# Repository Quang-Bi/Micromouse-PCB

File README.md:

# Micromouse-PCB
micromouse pcb I design for fun

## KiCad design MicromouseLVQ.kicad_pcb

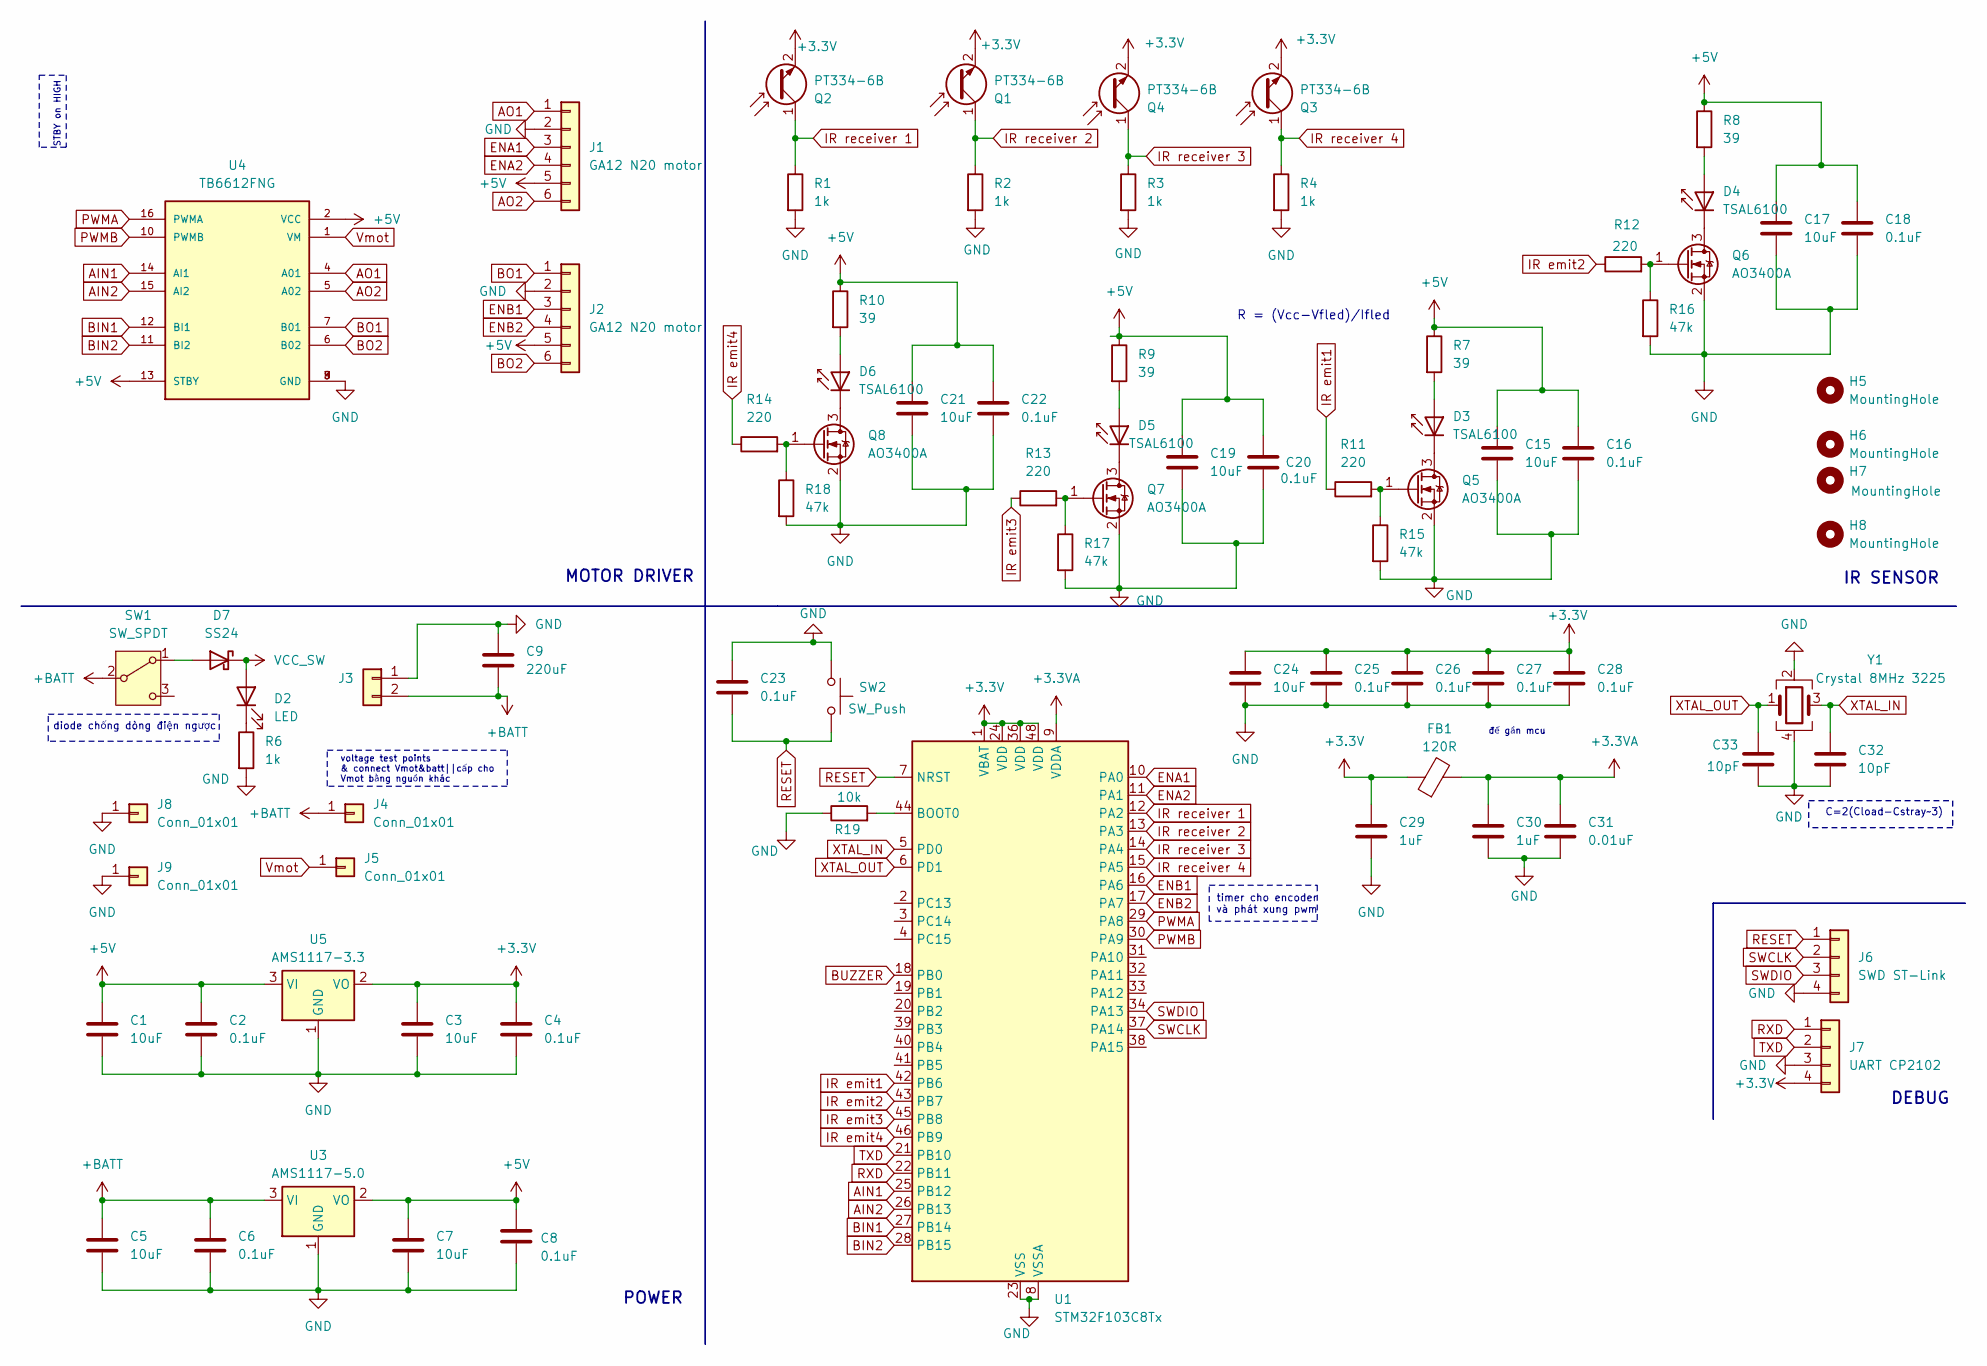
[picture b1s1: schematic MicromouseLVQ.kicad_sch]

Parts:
C1, C3, C5, C7, C15, C17, C19, C21, C24: 10uF; C_0603_1608Metric
C2, C4, C6, C8, C16, C18, C20, C22, C23, C25, C26, C27, C28: 0.1uF; C_0603_1608Metric
C9: 220uF; CP_Elec_4x4.5
C29, C30: 1uF; C_0603_1608Metric
C31: 0.01uF; C_0603_1608Metric
C32, C33: 10pF; C_0603_1608Metric
D2: LED; LED_0603_1608Metric
D3, D4, D5, D6: TSAL6100; LED_D5.0mm_Horizontal_O1.27mm_Z3.0mm_Clear
D7: SS24; D_SMA
FB1: 120R; LairdTech_28C0236-0JW-10
H5, H6, H7, H8: MountingHole; MountingHole_2.2mm_M2
J1, J2: GA12 N20 motor; PinHeader_1x06_P2.54mm_Vertical
J3: Conn_01x02; PinHeader_1x02_P2.54mm_Vertical
J4, J5, J8, J9: Conn_01x01; PinHeader_1x01_P2.54mm_Vertical
J6: SWD ST-Link; PinHeader_1x04_P2.54mm_Vertical
J7: UART CP2102; PinHeader_1x04_P2.54mm_Vertical
Q1, Q2, Q3, Q4: PT334-6B; LED_D5.0mm_Horizontal_O1.27mm_Z3.0mm_IRBlack
Q5, Q6, Q7, Q8: AO3400A; SOT-23
R1, R2, R3, R4, R6: 1k; R_0603_1608Metric
R7, R8, R9, R10: 39; R_0603_1608Metric
R11, R12, R13, R14: 220; R_0603_1608Metric
R15, R16, R17, R18: 47k; R_0603_1608Metric
R19: 10k; R_0603_1608Metric
SW1: SW_SPDT; SW_CK_JS202011CQN_DPDT_Straight
SW2: SW_Push; SW_Push_SPST_NO_Alps_SKRK
U1: STM32F103C8Tx; LQFP-48_7x7mm_P0.5mm
U3: AMS1117-5.0; SOT-223-3_TabPin2
U4: TB6612FNG; PARTREV 11-13-17
U5: AMS1117-3.3; SOT-223-3_TabPin2
Y1: Crystal 8MHz 3225; Crystal_SMD_3225-4Pin_3.2x2.5mm

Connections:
+3.3V: C3.1, C4.1, C24.1, C25.1, C26.1, C27.1, C28.1, C29.1, FB1.1, J7.4, Q1.2 (E), Q2.2 (E), Q3.2 (E), Q4.2 (E), U1.1 (VBAT), U1.24 (VDD), U1.36 (VDD), U1.48 (VDD), U5.2 (VO)
+3.3VA: C30.1, C31.1, FB1.2, U1.9 (VDDA)
+5V: C1.1, C2.1, C7.1, C8.1, C15.1, C16.1, C17.1, C18.1, C19.1, C20.1, C21.1, C22.1, J1.5, J2.5, R7.1, R8.1, R9.1, R10.1, U3.2 (VO), U4.2 (VCC), U4.13 (STBY), U5.3 (VI)
+BATT: C5.1, C6.1, C9.2, J3.2, J4.1, SW1.2 (B), U3.3 (VI)
AIN1: U1.25 (PB12), U4.14 (AI1)
AIN2: U1.26 (PB13), U4.15 (AI2)
AO1: J1.1, U4.4 (A01)
AO2: J1.6, U4.5 (A02)
BIN1: U1.27 (PB14), U4.12 (BI1)
BIN2: U1.28 (PB15), U4.11 (BI2)
BO1: J2.1, U4.7 (B01)
BO2: J2.6, U4.6 (B02)
BUZZER: U1.18 (PB0)
ENA1: J1.3, U1.10 (PA0)
ENA2: J1.4, U1.11 (PA1)
ENB1: J2.3, U1.16 (PA6)
ENB2: J2.4, U1.17 (PA7)
GND: C1.2, C2.2, C3.2, C4.2, C5.2, C6.2, C7.2, C8.2, C9.1, C15.2, C16.2, C17.2, C18.2, C19.2, C20.2, C21.2, C22.2, C23.1, C24.2, C25.2, C26.2, C27.2, C28.2, C29.2, C30.2, C31.2, C32.2, C33.2, J1.2, J2.2, J3.1, J6.4, J7.3, J8.1, J9.1, Q5.2 (S), Q6.2 (S), Q7.2 (S), Q8.2 (S), R1.2, R2.2, R3.2, R4.2, R6.2, R15.2, R16.2, R17.2, R18.2, R19.1, SW2.1, U1.8 (VSSA), U1.23 (VSS), U1.35 (VSS), U1.47 (VSS), U3.1 (GND), U4.3 (GND), U4.8 (GND), U4.9 (GND), U5.1 (GND), Y1.2, Y1.4
IR emit1: R11.1, U1.42 (PB6)
IR emit2: R12.1, U1.43 (PB7)
IR emit3: R13.1, U1.45 (PB8)
IR emit4: R14.1, U1.46 (PB9)
IR receiver 1: Q2.1 (C), R1.1, U1.12 (PA2)
IR receiver 2: Q1.1 (C), R2.1, U1.13 (PA3)
IR receiver 3: Q4.1 (C), R3.1, U1.14 (PA4)
IR receiver 4: Q3.1 (C), R4.1, U1.15 (PA5)
unnamed: D2.1 (K), R6.1
unnamed: D3.2 (A), R7.2
unnamed: D3.1 (K), Q5.3 (D)
unnamed: D4.2 (A), R8.2
unnamed: D4.1 (K), Q6.3 (D)
unnamed: D5.2 (A), R9.2
unnamed: D5.1 (K), Q7.3 (D)
unnamed: D6.2 (A), R10.2
unnamed: D6.1 (K), Q8.3 (D)
unnamed: D7.2 (A), SW1.1 (A)
unnamed: Q5.1 (G), R11.2, R15.1
unnamed: Q6.1 (G), R12.2, R16.1
unnamed: Q7.1 (G), R13.2, R17.1
unnamed: Q8.1 (G), R14.2, R18.1
unnamed: R19.2, U1.44 (BOOT0)
PWMA: U1.29 (PA8), U4.16 (PWMA)
PWMB: U1.30 (PA9), U4.10 (PWMB)
RESET: C23.2, J6.1, SW2.2, U1.7 (NRST)
RXD: J7.1, U1.22 (PB11)
SWCLK: J6.2, U1.37 (PA14)
SWDIO: J6.3, U1.34 (PA13)
TXD: J7.2, U1.21 (PB10)
VCC_SW: D2.2 (A), D7.1 (K)
Vmot: J5.1, U4.1 (VM)
XTAL_IN: C32.1, U1.5 (PD0), Y1.3
XTAL_OUT: C33.1, U1.6 (PD1), Y1.1

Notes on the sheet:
để gần mcu
timer cho encoder và phát xung pwm
R = (Vcc-Vfled)/Ifled
C=2(Cload-Cstray~3)
MOTOR DRIVER
IR SENSOR
diode chống dòng điện ngược
voltage test points & connect Vmot&batt||cấp cho Vmot bằng nguồn khác
POWER
STBY on HIGH
DEBUG

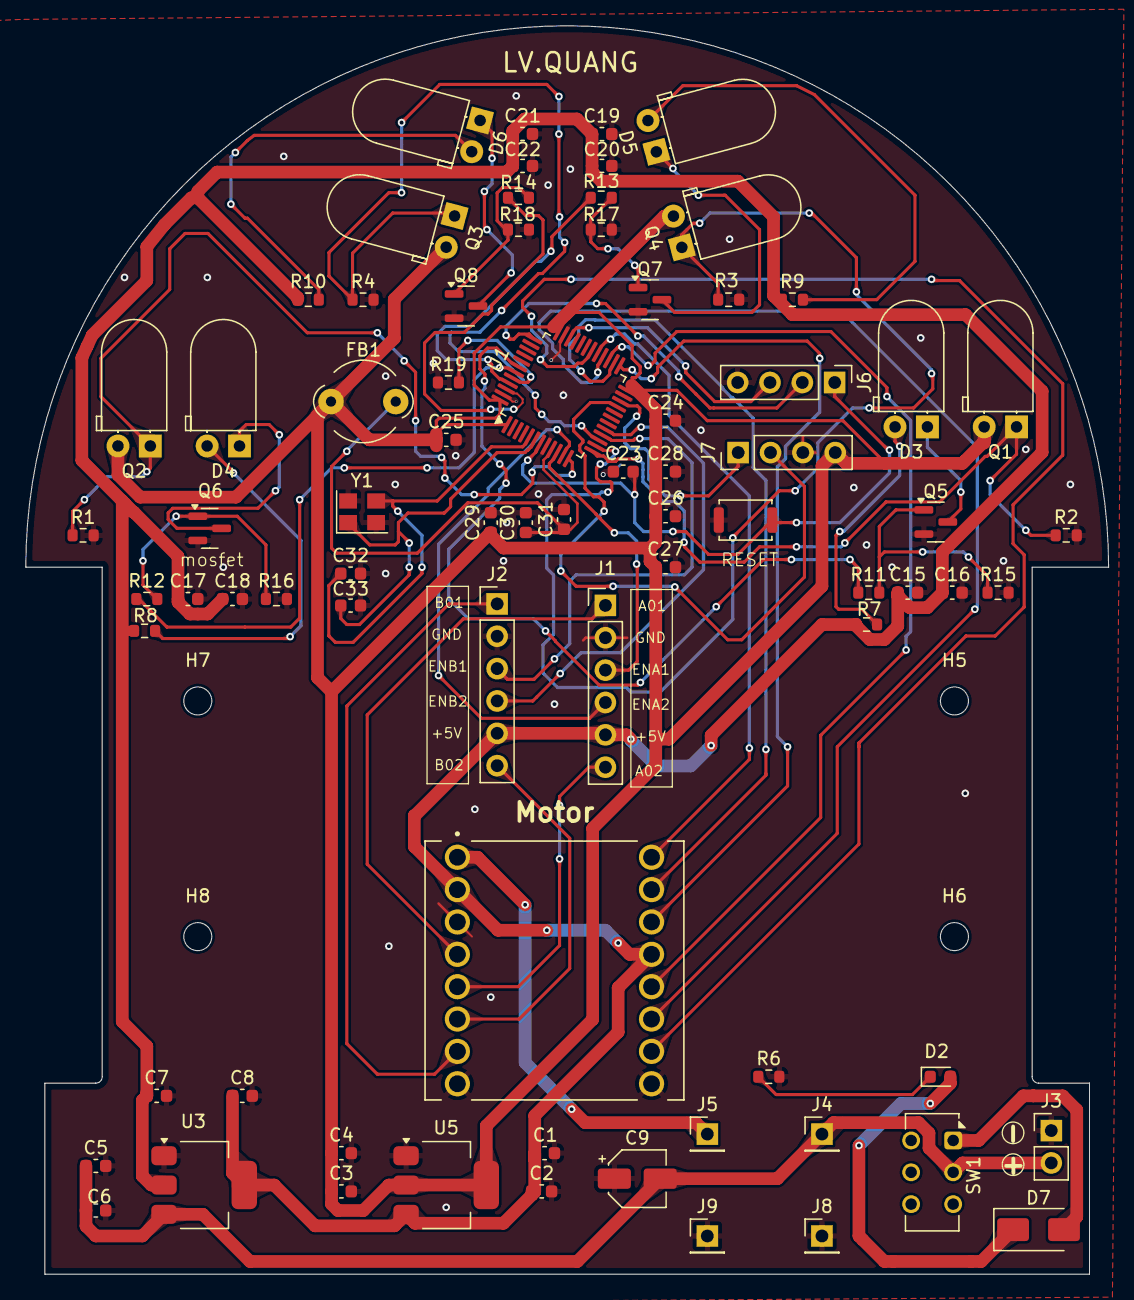
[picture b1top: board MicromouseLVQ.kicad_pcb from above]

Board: 2 copper layers, 85.0 x 98.0 mm, 81 parts (0 on the bottom side), 51 nets.
